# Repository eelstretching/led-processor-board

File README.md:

# LED processor board

The brains for the LED output boards: an RP2350B with an RM2 radio, 8 MB PSRAM, a DS3231 RTC and
four 16-pin ribbon shrouds. Each shroud drives one
[led-output-board](https://github.com/eelstretching/led-output-board), which does the level
shifting, fusing and strand connectors, so this board carries no LED power.

The core (RP2350B, flash, PSRAM, RM2, crystal, BOOTSEL/RUN buttons, 3.3 V regulator) is the
[rp2350b-rm2-reference](https://github.com/eelstretching/rp2350b-rm2-reference) schematic
unchanged, except that its micro-B USB is now USB-C. That board's single-row J2/J3 headers are
gone; the rest is new.

Status: **schematic and first layout done, not yet built.** ERC is clean apart from the four items
inherited from Pi's design, and DRC has no copper errors and nothing unconnected (see
"Verification").

All three sheets: [docs/schematic.pdf](docs/schematic.pdf) ([Power](docs/sheet-power.png), [Outputs](docs/sheet-outputs.png)).

## Pin map

| GPIO | Use |
|---|---|
| 0-7 | OUT1 (J5) data 1-8 |
| 8-15 | OUT2 (J6) data 1-8 |
| 16-23 | OUT3 (J7) data 1-8 |
| 24-31 | OUT4 (J8) data 1-8 |
| 32 | RTC SDA (I2C0), 10k pull-up |
| 33 | RTC SCL (I2C0), 10k pull-up |
| 34 | RTC INT/SQW, 10k pull-up (open drain) |
| 35-42 | J2 spare header (UART1 TX/RX on 36/37; 40-42 are ADC0-2) |
| 43-46 | RM2 (WL_ON + BT_ON, CS, DATA, CLK), as on the reference board |
| 47 | PSRAM chip select, as on the reference board |

All 32 outputs sit in GPIO 0-31, so one PIO block (GPIO base 0) reaches every output. The radio's
PIO uses the 16-47 window, so it has to be a different PIO block from the LED renderer's. The
board header is `firmware/boards/led_processor_board.h` (the reference board's `rp2350b_rm2.h`
plus the RTC pins); see [firmware/README.md](firmware/README.md) for the DS3231 driver and the
`rtc_set` firmware.

## Output shrouds (J5-J8)

The same pinout as the output boards' J2 (and MegaTree `docs/power.md`). Pin 1 is the triangle on
the shroud.

| Pin | Signal | Pin | Signal |
|---|---|---|---|
| 1 | GND | 2 | data 1 |
| 3 | GND | 4 | data 2 |
| 5 | GND | 6 | data 3 |
| 7 | GND | 8 | data 4 |
| 9 | GND | 10 | data 5 |
| 11 | GND | 12 | data 6 |
| 13 | +3V3 (shifter VCCA) | 14 | data 7 |
| 15 | +5V (shifter VCCB) | 16 | data 8 |

Data n of OUTk is GPIO 8(k-1) + (n-1). Each data line has a 33R series resistor at the RP2350 end
to damp ringing on the ribbon. Each shroud has 100n on +3V3 and on +5V.

## Power (Power sheet)

- **J4, 12 V in**, from the LED supply (through a PTC on an output board, as planned for the Pico
  boards). D3 (SS34) blocks a reversed lead.
- **U7, TPS54202H buck, 12 V to 5 V.** 4.5-28 V in, 2 A, SOT-23-6, with the values from TI's
  TPS54202HEVM-716 5 V design: 100k/13.3k divider (5.08 V), 75 pF feed-forward, 15 uH, 3 x 22 uF out,
  510k EN pull-up from 12 V. The load is well under 0.5 A.
- **+5V goes straight to pin 15 of every shroud**, and through D4 (B5819W) to VSYS, which feeds the
  existing NCP1117 3.3 V regulator. **+3V3 goes to pin 13 of every shroud.**
- D5 (green) shows +5V is up.
- USB still works for programming. On USB alone the board runs (VSYS through D2), but the ribbons
  get no +5V, so the output boards' shifters are off. D4 keeps USB from back-feeding the buck.

## USB

J1 is a USB-C receptacle (Korean Hroparts TYPE-C-31-M-12, LCSC C165948, KiCad's stock
`USB_C_Receptacle_HRO_TYPE-C-31-M-12` footprint) in place of Pi's micro-B. USB 2.0 only: D+ and D-
from both sides of the plug are joined, CC1 and CC2 each have a 5.1k pull-down (R56, R57) so a
USB-C charger or host turns on 5 V, SBU1/SBU2 are unconnected and the shell goes to GND. The
D+/D- nets (USB_D+/USB_D-, through Pi's 27R R7/R8) and VBUS into D2 are as before.

## RTC

The DS3231 circuit from universal-strip-controller (its U9): DS3231SN, 1 uF on VCC, 10k pull-ups on
SDA, SCL and INT/SQW, 32KHZ and RST unconnected. The coin cell is a CR1220 in a Keystone 3001 holder,
so it can be replaced (universal-strip-controller used a tabbed cell).

## Headers

- **J2, spare GPIO** (1x10, 2.54 mm): 3V3, GPIO35-42, GND.
- **J3, SWD** (1x3, 2.54 mm): SWCLK, GND, SWD, the same order as a Pico's debug header.
- **J9, RM2 spare GPIO** (1x3, 2.54 mm, under the board name, left of J3): WL_GPIO1, WL_GPIO2, GND. These are the
  radio chip's own pins, not RP2350 pins: set or read them with `cyw43_arch_gpio_put()` /
  `cyw43_arch_gpio_get()`, which go over the radio's SPI link, so they're slow, plain digital in/out
  (no PWM, PIO or ADC). Fine for an LED, a button or a relay in a pinch. On a Pico 2 W these two are
  SMPS mode and VBUS sense; here nothing else uses them.

## BOM / JLCPCB

`production/` holds the BOMs and the JLCPCB upload set. `bom-full.csv` is the full BOM with LCSC
numbers (edit this one); the rest is made from it and the board by
`python3 tools/jlc.py` (rerun it after any board change):

- `led-processor-board-gerbers.zip`: gerbers and drill files.
- `jlcpcb-bom.csv` and `jlcpcb-cpl.csv`: BOM and placement for the 111 SMD parts JLC assembles
  (everything on the top side with an LCSC number). JLC's 3D models don't always share KiCad's zero
  angle: `ROT_FIX` in `tools/jlc.py` turns U2, U3, U4 and U6 a quarter turn to match (checked in
  JLC's placement preview for the first order). Still check the preview: legs on pads, pink pin-1
  dot at the board's pin-1 mark.

`tools/jlc.py` needs KiCad's own Python (for `pcbnew`) and `kicad-cli` on the PATH. On a Mac with
KiCad in `/Applications/KiCad`, save the board in KiCad, then from the repo root:

```sh
K=/Applications/KiCad/KiCad.app/Contents
PATH=$K/MacOS:$PATH $K/Frameworks/Python.framework/Versions/Current/bin/python3 tools/jlc.py
git status production/   # see what changed, then commit and push
```

On Linux, with KiCad installed from its PPA, plain `python3 tools/jlc.py` works. The BOM and CPL
only change when parts move or the BOM changes; the gerbers zip changes with any copper or silk
edit.

Left off both files for hand-soldering:

- **U5 RM2**: buy Raspberry Pi SC1169, as on the reference board.
- **L1** Abracon AOTA-B201610S3R3-101-T, 3.3 uH (Digi-Key or Mouser): the part Pi specifies for the RP2350 core regulator, out of stock at LCSC when ordering (2026-10). It is polarized: match its dot to the footprint mark.
- **BT1** Keystone 3001 holder (Digi-Key 36-3001-ND).
- **J2, J3, J9** pin headers and **J5-J8** box headers (the shrouds already bought for the output
  boards).
- **J4** terminal block (C695629): JLC could fit it as through-hole assembly, but it's left to you.

SW1/SW2 are XKB TS-1088R-02526 (C455281, 4 x 3 mm) in place of Pi's Wurth 434133025816, which LCSC
doesn't stock; same spots, same nets. R1 is DNP, as on the reference board. Pi's R9 (an unfitted 0R option from GPIO0 to the flash chip
select) is removed, with its GPIO0 branch, so OUT1's first data line has no stub. The PSRAM chip
select is GPIO47 (QMI CS1n, RP2350 datasheet section 9.4, which allows GPIO 0, 8, 19 or 47).

J4 (DORABO DB301V-3.5-2P, C695629) is in the same family as the output boards' strand terminals and
uses KiCad's stock 3.5 mm Phoenix PT footprint; check the hole size against the DB301V drawing when
laying out.

## Layout

100 x 89.5 mm, **2 layers**, four 2.75 mm (M2.5) mounting holes. 3D views:
[top](docs/pcb-3d-top.png), [bottom](docs/pcb-3d-bottom.png); bottom copper:
[docs/pcb-bottom-copper.png](docs/pcb-bottom-copper.png).

- **The core is Pi's layout**: the RP2350B, flash, crystal, regulator, buttons and RM2 keep their
  placement and routing from the reference board (the buttons are a stock LCSC part in Pi's spots).
  The one move: **U4 (PSRAM), C22, R11 and R13
  moved from under the flash to the top side**, just left of it, so every part is on the top and
  JLCPCB can assemble one side. The PSRAM's QSPI branches are about 12-15 mm long; Pi's were vias
  straight down to it. Pi's +3V3 top pour and full GND bottom plane stay; the board widens with a top
  GND pour on either side, stitched to the bottom plane.
- **Shrouds**: OUT1/OUT2 (J5, J6) down the left edge, OUT3/OUT4 (J7, J8) along the bottom, either
  side of the RM2 antenna. The bottom two sit as low as the antenna strip allows (their bottom pins
  stop just above it, their bodies overhang it); J8 is 1.6 mm left of the resistor row to clear the
  corner hole, so its data lines jog. The 33R resistors sit in a row next to each shroud's data
  pins. On J7/J8 the 3V3 and 5V runs use the channel between the two pin rows, one net per layer.
- **Power** in the top right: J4 (12 V) on the right edge, D3, the TPS54202 buck (U7, L2, output
  caps) and D5. The 12 V runs are 0.8 mm, +5V 0.5 mm.
- **USB-C** at the top edge where Pi's micro-B was, with **J2 (spare GPIO35-42, plus 3V3 and GND)**
  along the top edge to its right, so wires leave from the board edge. Its lines leave the core on
  the top layer, drop through a row of vias left of the buck and fan out on the bottom; the ADC pins
  (GPIO40-42) are the lanes furthest from the buck's switch node. The RTC (U6, BT1) is on the right
  and J9 (RM2 spare GPIO) and J3 (SWD) sit side by side under the board name.
- The antenna keepout runs the full width along the bottom edge past the RM2.

### Regenerating it

The layout was built by scripts in `tools/pcb/` (KiCad 10 Python API plus Freerouting 1.9.0). From
here on it is a normal KiCad board, so edit it in KiCad; the scripts are a record of how it was made.

1. `build_pcb.py REF.kicad_pcb net.xml OUT.kicad_pcb .` loads the reference layout, drops its
   micro-B and headers, clips the routes that went to them, places the new parts
   (`placement.py`) and hand-routes the power, USB-C, OUT4, RM2 and SWD runs (`preroute.py`).
   `net.xml` is `kicad-cli sch export netlist --format kicadxml`.
2. `route.sh in out 20` exports a Specctra DSN, freezes the existing copper and sets net classes
   (`dsn_prep.py`), runs Freerouting 1.9.0 (`xvfb-run java -jar freerouting-1.9.0.jar`; 2.x
   ignores the pass limit and never writes the session), and imports the result.
3. `post.py` trims dangling tails and adds GND stitching vias; `fix.py` adds the two +3V3 jumpers
   under the +5V run to J7 and C40's link; `rip.py` plus a second `route.sh` rerouted the J2/RTC
   fan-out (GPIO32-42), which the first pass left one net short on; `silk.py` places the reference
   designators.
4. Moving the PSRAM to the top: `psram.py` (flip and place U4/C22/R11/R13, rip their bottom-side
   routing), `post.py --trim-only`, `psram2.py` (Pi's QSPI escapes from under U3, the GPIO47 drop),
   `route.sh`, then the U4 supply hop at the end of `fix.py`, `post.py` and `silk.py`.
5. Moving J2 to the top edge: `j2top.py` (place it and its pin labels, rip its old fan-out),
   `post.py --trim-only`, `j2route.py` (hand-routes the bus and moves the +3V3 hop from the core pour
   to the RTC, which also feeds the lower pour and the RM2, below the via row), `post.py`, `silk.py`.
6. Bottom shrouds to the edge and J9: `shrouds.py` (move J7/J8 and their caps, re-run the data
   lines, rip their power), `shrouds2.py` (hand-routes their 3V3/5V), `post.py`, `silk.py`, then
   `hdrs.py` (adds J9 and moves J3 under the board name), `route.sh` (WL_GPIO1/2), `post.py`,
   `silk.py`, and `swd.py` (hand-routes SWCLK/SWD, which Freerouting couldn't get out of the core).
7. LCSC buttons: `buttons.py` (TS-1088R footprints in SW1/SW2's spots, stubs re-joined) and
   `tools/sch_buttons.py` (swaps the schematic symbols to `Switch:SW_Push`).
8. `tools/rm_r9.py` drops R9 and its GPIO0 branch from the schematic and board; `tidy_gpio.py`
   straightens GPIO0 and chamfers GPIO1 on their way to OUT1.
9. `render.sh` / `rendernz.sh` make the PNGs (`kicad-cli pcb export svg` cropped with cairosvg;
   `rendernz` hides zone fills).

## Files

| Path | What |
|---|---|
| `led-processor-board.kicad_sch` | root sheet: the reference core, RTC, J2/J3/J9, sheet symbols |
| `Power.kicad_sch` | 12 V in, buck, +5V, VSYS |
| `Outputs.kicad_sch` | J5-J8 shrouds, 33R series resistors, decoupling |
| `rp2350b_rm2.kicad_sym`, `rp2350b_rm2.pretty/` | RM2 symbol and footprint (from the reference) |
| `production/bom-full.csv` | full BOM with LCSC numbers |
| `production/` (rest) | JLCPCB gerbers zip, assembly BOM and CPL (`tools/jlc.py`) |
| `docs/schematic.pdf`, `docs/sheet-*.png` | all three sheets |
| `led-processor-board.kicad_pcb` | the layout |
| `docs/pcb-*.png` | layout previews |
| `tools/build_schematic.py` | the one-off script that built these sheets from the reference (kept for reference; edit the schematic in KiCad from here on) |
| `tools/pcb/` | the scripts that built the layout (see "Regenerating it") |

## Verification

`kicad-cli sch erc` (KiCad 10.0.7, stock libraries) reports the same four items as the reference
board, all in Pi's part of the design: U2's two OUT pins tied together, U1 VREG_AVDD and #PWR16
"not driven" (power-flag nits), and one off-grid wire end. The rest are notes that Pi's embedded
libraries (`RPI_DB`, `RPI - Power`, `RPI_COMPILED`) aren't in the library table, as on the
reference board. A netlist check confirms each shroud's GND, +3V3, +5V and data pins, the RTC nets
and the 12 V to VSYS chain.

`kicad-cli pcb drc --severity-all --schematic-parity` reports no clearance, short, hole or unconnected
items, and the board matches the schematic (apart from footprints not carrying the symbols'
`manufacturer` fields). What's
left: 41 warnings that Pi's `RPI_COMPILED` footprint library isn't in the library table (as on the
reference board), and 4 silkscreen-past-the-edge warnings from J1 and J4, whose bodies overhang the
board edge (the USB-C opening and the terminal block). C7 and C27 have their reference designators hidden
for lack of room.

## License

Raspberry Pi's design is MIT (see `LICENSE-RaspberryPi.txt`); the additions here are MIT too.

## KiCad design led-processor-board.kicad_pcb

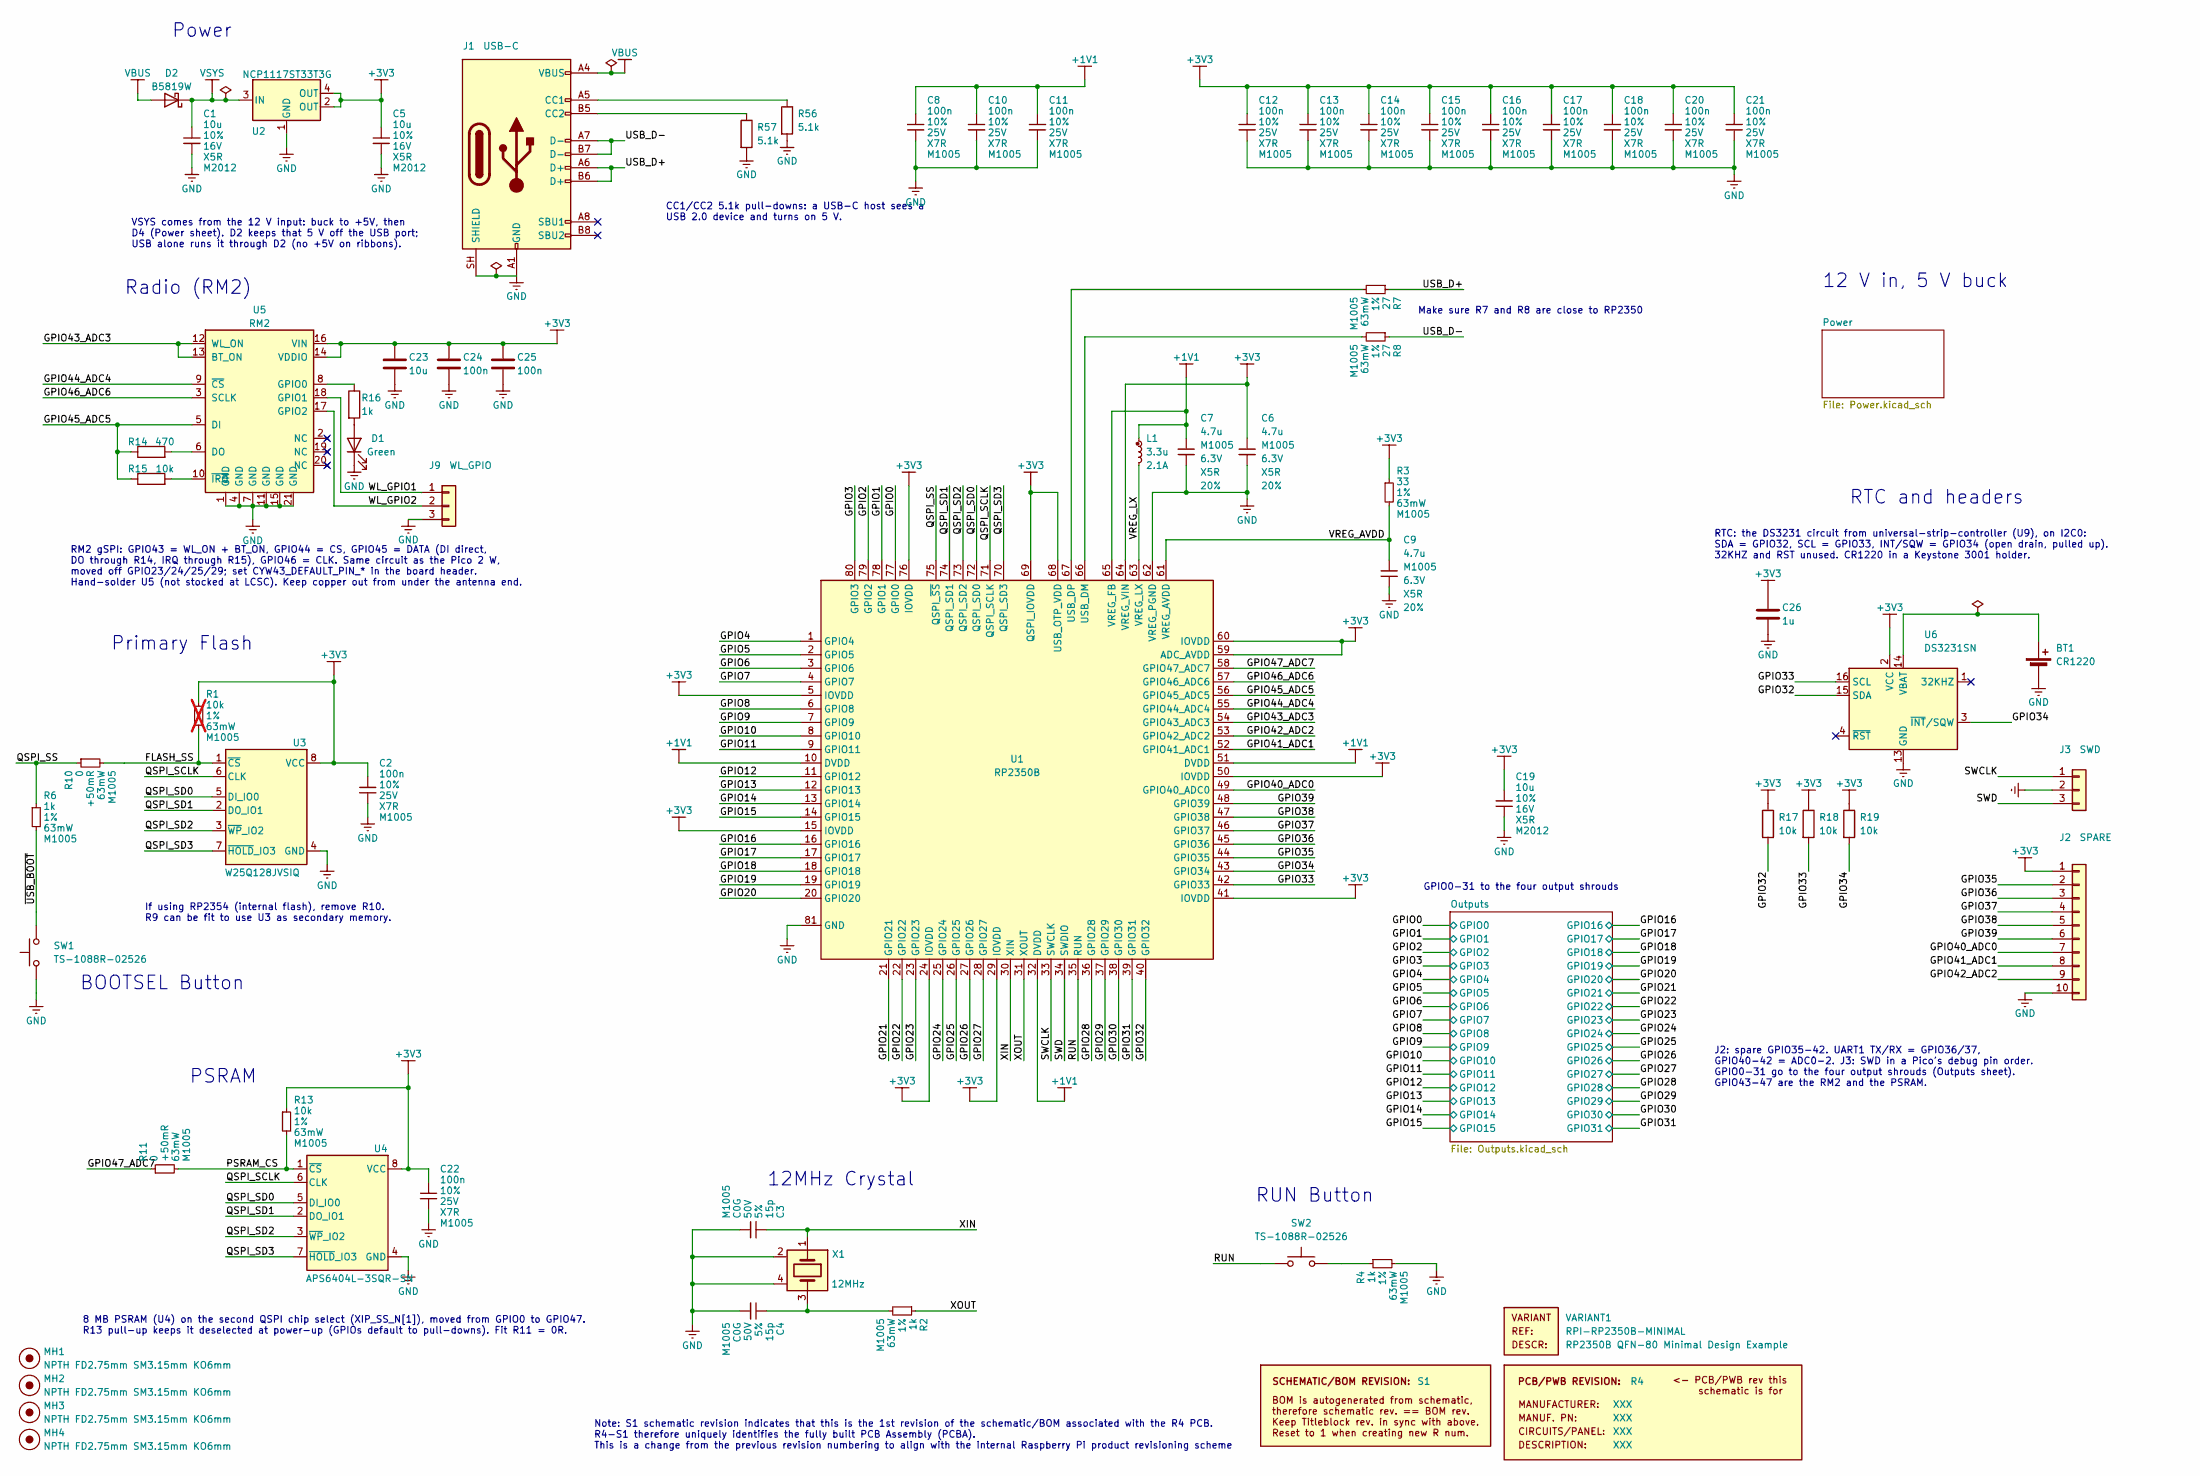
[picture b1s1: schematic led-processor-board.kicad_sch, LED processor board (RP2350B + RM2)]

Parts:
BT1: CR1220; BatteryHolder_Keystone_3001_1x12mm; manufacturer_pn 3001
C1, C5, C19: 10u; generic_capc2012x125; voltage 16V; tolerance 10%; part_uid RP-01GYSK-AVBE41; LCSC C15850
C2, C8, C10, C11, C12, C13, C14, C15, C16, C17, C18, C20, C21, C22: 100n; generic_capc1005x50; voltage 25V; tolerance 10%; part_uid RP-01BJ9Y-KRGF41; LCSC C1525
C3, C4: 15p; generic_capc1005x50; voltage 50V; tolerance 5%; part_uid RP-01C89W-LLY9XV; LCSC C1548
C6, C7: 4.7u; generic_capc1005x50_wide; voltage 6.3V; tolerance 20%; part_uid RP-019A1P-0C2GHY; LCSC C23733
C9: 4.7u; generic_capc1005x50; voltage 6.3V; tolerance 20%; part_uid RP-019A1P-0C2GHY; LCSC C23733
C23: 10u; C_0805_2012Metric; manufacturer_pn CL21A106KAYNNNE; LCSC C15850
C24, C25: 100n; C_0402_1005Metric; manufacturer_pn CL05B104KO5NNNC; LCSC C1525
C26: 1u; C_0402_1005Metric; manufacturer_pn CL05A105KA5NQNC; LCSC C52923
D1: Green; LED_0603_1608Metric; manufacturer_pn KT-0603YG; LCSC C2289
D2: B5819W; D_SOD-123; manufacturer_pn B5819W SL; LCSC C8598
J1: USB-C; USB_C_Receptacle_HRO_TYPE-C-31-M-12; manufacturer_pn TYPE-C-31-M-12; LCSC C165948
J2: SPARE; PinHeader_1x10_P2.54mm_Vertical; manufacturer_pn 1x10 2.54 mm pin header
J3: SWD; PinHeader_1x03_P2.54mm_Vertical; manufacturer_pn 1x3 2.54 mm pin header
J9: WL_GPIO; PinHeader_1x03_P2.54mm_Vertical; manufacturer_pn 1x3 2.54 mm pin header
L1: 3.3u; abracon_aota-b201610s3r3-101-t; tolerance 20%; part_uid RP-01GY5D-2VC7WP; LCSC C42411119
MH1, MH2, MH3, MH4: NPTH FD2.75mm SM3.15mm KO6mm; none_mh_npth_fd2p75mm_sm3p15mm_ko6mm; part_uid RP-01HF5R-LCTEJS
PCB1: R4; manufacturer_pn XXX
R1: 10k; generic_resc1005x35; tolerance 1%; voltage 50V; part_uid RP-019A1P-53DHSX; LCSC C25744; not fitted
R2, R4, R6: 1k; generic_resc1005x35; tolerance 1%; voltage 50V; part_uid RP-019A1P-4Z6ZWY; LCSC C11702
R3: 33; generic_resc1005x35; tolerance 1%; voltage 50V; part_uid RP-019A1P-58PW9L; LCSC C25105
R7, R8: 27; generic_resc1005x35; tolerance 1%; voltage 50V; part_uid RP-01C89V-LTEYC4; LCSC C25100
R10, R11: 0; generic_resc1005x35; tolerance +50mR; voltage 50V; part_uid RP-019A1P-4Y4V63; LCSC C17168
R13: 10k; generic_resc1005x35; tolerance 1%; voltage 50V; part_uid RP-019A1P-53DHSX; LCSC C25744
R14: 470; R_0402_1005Metric; manufacturer_pn 0402WGF4700TCE; LCSC C25117
R15, R17, R18, R19: 10k; R_0402_1005Metric; manufacturer_pn 0402WGF1002TCE; LCSC C25744
R16: 1k; R_0402_1005Metric; manufacturer_pn 0402WGF1001TCE; LCSC C11702
R56, R57: 5.1k; R_0402_1005Metric; manufacturer_pn 0402WGF5101TCE; LCSC C25905
SBREV1: S1
SW1, SW2: TS-1088R-02526; SW_SPST_TS-1088-xR025; manufacturer_pn TS-1088R-02526; LCSC C455281
U1: RP2350B; rpi_rp2350b_vias; part_uid RP-01HA9H-ABBLJN; LCSC C42415655
U2: NCP1117ST33T3G; onsemi_ncp1117st33t3g; voltage 3.3V; part_uid RP-01JWD9-7JRX6J; LCSC C26537
U3: W25Q128JVSIQ; generic_soic127p790x195-8; voltage 2.7-3.6V; part_uid RP-01JWD4-F1H4N9; LCSC C97521
U4: APS6404L-3SQR-SN; SOIC-8_3.9x4.9mm_P1.27mm; voltage 2.7-3.6V; manufacturer_pn APS6404L-3SQR-SN; LCSC C5333729
U5: RM2; RPi_RM2; manufacturer_pn SC1169 (RMC20452T)
U6: DS3231SN; SOIC-16W_7.5x10.3mm_P1.27mm; manufacturer_pn DS3231SN#T&R; LCSC C9866
VARIANT1: RPI-RP2350B-MINIMAL
X1: 12MHz; generic_xtalcc320x250x80-4; tolerance 30ppm; part_uid RP-01G8X7-GS352B; LCSC C20625731

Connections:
+1V1: C7.1, C8.1, C10.1, C11.1, L1.1, U1.10 (DVDD), U1.32 (DVDD), U1.51 (DVDD), U1.65 (VREG_FB)
+3V3: C2.1, C5.1, C6.1, C12.1, C13.1, C14.1, C15.1, C16.1, C17.1, C18.1, C19.1, C20.1, C21.1, C22.1, C23.1, C24.1, C25.1, C26.1, J2.1, R1.1, R3.1, R13.1, R17.1, R18.1, R19.1, U1.5 (IOVDD), U1.15 (IOVDD), U1.24 (IOVDD), U1.29 (IOVDD), U1.41 (IOVDD), U1.50 (IOVDD), U1.59 (ADC_AVDD), U1.60 (IOVDD), U1.64 (VREG_VIN), U1.68 (USB_OTP_VDD), U1.69 (QSPI_IOVDD), U1.76 (IOVDD), U2.2 (OUT), U2.4 (OUT), U3.8 (VCC), U4.8 (VCC), U5.14 (VDDIO), U5.16 (VIN), U6.2 (VCC); also elsewhere on the board
/FLASH_SS: R1.2, R10.2, U3.1 (~CS)
/GPIO0: U1.77 (GPIO0); also elsewhere on the board
/GPIO1: U1.78 (GPIO1); also elsewhere on the board
/GPIO2: U1.79 (GPIO2); also elsewhere on the board
/GPIO3: U1.80 (GPIO3); also elsewhere on the board
/GPIO4: U1.1 (GPIO4); also elsewhere on the board
/GPIO5: U1.2 (GPIO5); also elsewhere on the board
/GPIO6: U1.3 (GPIO6); also elsewhere on the board
/GPIO7: U1.4 (GPIO7); also elsewhere on the board
/GPIO8: U1.6 (GPIO8); also elsewhere on the board
/GPIO9: U1.7 (GPIO9); also elsewhere on the board
/GPIO10: U1.8 (GPIO10); also elsewhere on the board
/GPIO11: U1.9 (GPIO11); also elsewhere on the board
/GPIO12: U1.11 (GPIO12); also elsewhere on the board
/GPIO13: U1.12 (GPIO13); also elsewhere on the board
/GPIO14: U1.13 (GPIO14); also elsewhere on the board
/GPIO15: U1.14 (GPIO15); also elsewhere on the board
/GPIO16: U1.16 (GPIO16); also elsewhere on the board
/GPIO17: U1.17 (GPIO17); also elsewhere on the board
/GPIO18: U1.18 (GPIO18); also elsewhere on the board
/GPIO19: U1.19 (GPIO19); also elsewhere on the board
/GPIO20: U1.20 (GPIO20); also elsewhere on the board
/GPIO21: U1.21 (GPIO21); also elsewhere on the board
/GPIO22: U1.22 (GPIO22); also elsewhere on the board
/GPIO23: U1.23 (GPIO23); also elsewhere on the board
/GPIO24: U1.25 (GPIO24); also elsewhere on the board
/GPIO25: U1.26 (GPIO25); also elsewhere on the board
/GPIO26: U1.27 (GPIO26); also elsewhere on the board
/GPIO27: U1.28 (GPIO27); also elsewhere on the board
/GPIO28: U1.36 (GPIO28); also elsewhere on the board
/GPIO29: U1.37 (GPIO29); also elsewhere on the board
/GPIO30: U1.38 (GPIO30); also elsewhere on the board
/GPIO31: U1.39 (GPIO31); also elsewhere on the board
/GPIO32: R17.2, U1.40 (GPIO32), U6.15 (SDA)
/GPIO33: R18.2, U1.42 (GPIO33), U6.16 (SCL)
/GPIO34: R19.2, U1.43 (GPIO34), U6.3 (~INT/SQW)
/GPIO35: J2.2, U1.44 (GPIO35)
/GPIO36: J2.3, U1.45 (GPIO36)
/GPIO37: J2.4, U1.46 (GPIO37)
/GPIO38: J2.5, U1.47 (GPIO38)
/GPIO39: J2.6, U1.48 (GPIO39)
/GPIO40_ADC0: J2.7, U1.49 (GPIO40_ADC0)
/GPIO41_ADC1: J2.8, U1.52 (GPIO41_ADC1)
/GPIO42_ADC2: J2.9, U1.53 (GPIO42_ADC2)
/GPIO43_ADC3: U1.54 (GPIO43_ADC3), U5.12 (WL_ON), U5.13 (BT_ON)
/GPIO44_ADC4: U1.55 (GPIO44_ADC4), U5.9 (~CS)
/GPIO45_ADC5: R14.1, R15.1, U1.56 (GPIO45_ADC5), U5.5 (DI)
/GPIO46_ADC6: U1.57 (GPIO46_ADC6), U5.3 (SCLK)
/GPIO47_ADC7: R11.1, U1.58 (GPIO47_ADC7)
/PSRAM_CS: R11.2, R13.2, U4.1 (~CS)
/QSPI_SCLK: U1.71 (QSPI_SCLK), U3.6 (CLK), U4.6 (CLK)
/QSPI_SD0: U1.72 (QSPI_SD0), U3.5 (DI_IO0), U4.5 (DI_IO0)
/QSPI_SD1: U1.74 (QSPI_SD1), U3.2 (DO_IO1), U4.2 (DO_IO1)
/QSPI_SD2: U1.73 (QSPI_SD2), U3.3 (~WP_IO2), U4.3 (~WP_IO2)
/QSPI_SD3: U1.70 (QSPI_SD3), U3.7 (~HOLD_IO3), U4.7 (~HOLD_IO3)
/QSPI_SS: R6.1, R10.1, U1.75 (QSPI_~SS)
/RUN: SW2.2, U1.35 (RUN)
/SWCLK: J3.1, U1.33 (SWCLK)
/SWD: J3.3, U1.34 (SWDIO)
/USB_D+: J1.A6 (D+), J1.B6 (D+), R7.1
/USB_D-: J1.A7 (D-), J1.B7 (D-), R8.1
/VREG_AVDD: C9.1, R3.2, U1.61 (VREG_AVDD)
/VREG_LX: L1.2, U1.63 (VREG_LX)
/WL_GPIO1: J9.1, U5.18 (GPIO1)
/WL_GPIO2: J9.2, U5.17 (GPIO2)
/XIN: C3.1, U1.30 (XIN), X1.1
/XOUT: R2.1, U1.31 (XOUT)
/~USB_BOOT: R6.2, SW1.2
GND: BT1.2 (-), C1.2, C2.2, C3.2, C4.2, C5.2, C6.2, C7.2, C8.2, C9.2, C10.2, C11.2, C12.2, C13.2, C14.2, C15.2, C16.2, C17.2, C18.2, C19.2, C20.2, C21.2, C22.2, C23.2, C24.2, C25.2, C26.2, D1.1 (K), J1.A1 (GND), J1.A12 (GND), J1.B1 (GND), J1.B12 (GND), J1.SH (SHIELD), J2.10, J3.2, J9.3, R4.2, R56.2, R57.2, SW1.1, U1.62 (VREG_PGND), U1.81 (GND), U2.1 (GND), U3.4 (GND), U4.4 (GND), U5.1 (GND), U5.4 (GND), U5.7 (GND), U5.11 (GND), U5.15 (GND), U5.21 (GND), U6.5 (GND), U6.6 (GND), U6.7 (GND), U6.8 (GND), U6.9 (GND), U6.10 (GND), U6.11 (GND), U6.12 (GND), U6.13 (GND), X1.2, X1.4; also elsewhere on the board
unnamed: BT1.1 (+), U6.14 (VBAT)
unnamed: C4.1, R2.2, X1.3
unnamed: D1.2 (A), R16.2
unnamed: J1.A5 (CC1), R56.1
unnamed: J1.B5 (CC2), R57.1
unnamed: R4.1, SW2.1
unnamed: R8.2, U1.66 (USB_DM)
unnamed: R7.2, U1.67 (USB_DP)
unnamed: R14.2, U5.6 (DO)
unnamed: R16.1, U5.8 (GPIO0)
unnamed: R15.2, U5.10 (~IRQ)
VBUS: D2.2 (A), J1.A4 (VBUS), J1.A9 (VBUS), J1.B4 (VBUS), J1.B9 (VBUS)
VSYS: C1.1, D2.1 (K), U2.3 (IN); also elsewhere on the board

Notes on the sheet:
8 MB PSRAM (U4) on the second QSPI chip select (XIP_SS_N[1]), moved from GPIO0 to GPIO47. R13 pull-up keeps it deselected at power-up (GPIOs default to pull-downs). Fit R11 = 0R.
RTC and headers
If using RP2354 (internal flash), remove R10. R9 can be fit to use U3 as secondary memory.
Note: S1 schematic revision indicates that this is the 1st revision of the schematic/BOM associated with the R4 PCB. R4-S1 therefore uniquely identifies the fully built PCB Assembly (PCBA). This is a change from the previous revision numbering to align with the internal Raspberry Pi product revisio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
Radio (RM2)
RUN Button
RM2 gSPI: GPIO43 = WL_ON + BT_ON, GPIO44 = CS, GPIO45 = DATA (DI direct, DO through R14, IRQ through R15), GPIO46 = CLK. Same circuit as the Pico 2 W, moved off GPIO23/24/25/29; set CYW43_DEFAULT_PIN_* in the board header. Hand-solder U5 (not stocked at LCSC). Keep copper out from under the antenna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
Primary Flash
BOOTSEL Button
12MHz Crystal
Make sure R7 and R8 are close to RP2350
PSRAM
Power
VSYS comes from the 12 V input: buck to +5V, then D4 (Power sheet). D2 keeps that 5 V off the USB port; USB alone runs it through D2 (no +5V on ribbons).
RTC: the DS3231 circuit from universal-strip-controller (U9), on I2C0: SDA = GPIO32, SCL = GPIO33, INT/SQW = GPIO34 (open drain, pulled up). 32KHZ and RST unused. CR1220 in a Keystone 3001 holder.
J2: spare GPIO35-42. UART1 TX/RX = GPIO36/37, GPIO40-42 = ADC0-2. J3: SWD in a Pico's debug pin order. GPIO0-31 go to the four output shrouds (Outputs sheet). GPIO43-47 are the RM2 and the PSRAM.
CC1/CC2 5.1k pull-downs: a USB-C host sees a USB 2.0 device and turns on 5 V.
GPIO0-31 to the four output shrouds
12 V in, 5 V buck

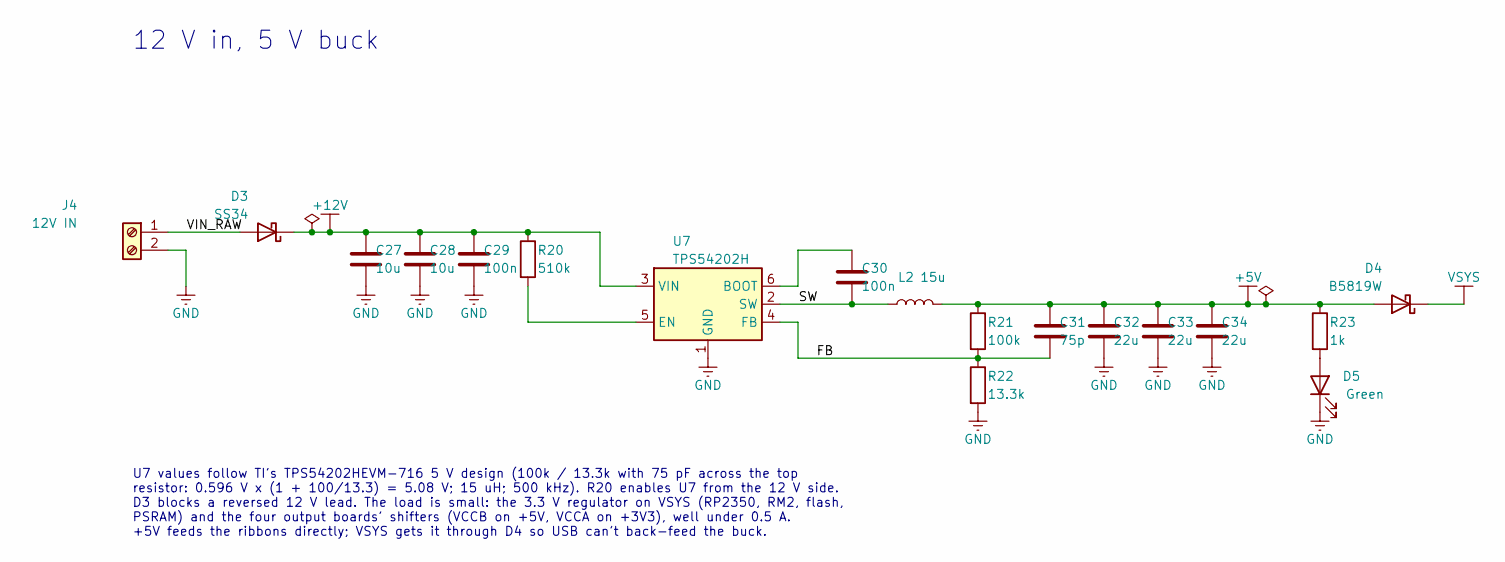
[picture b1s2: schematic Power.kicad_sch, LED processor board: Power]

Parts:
C27, C28: 10u; C_0805_2012Metric; manufacturer_pn CL21A106KBYNNNE; LCSC C440198
C29, C30: 100n; C_0603_1608Metric; manufacturer_pn CC0603KRX7R9BB104; LCSC C14663
C31: 75p; C_0402_1005Metric; manufacturer_pn 0402CG750J500NT; LCSC C37809
C32, C33, C34: 22u; C_0805_2012Metric; manufacturer_pn CL21A226MAQNNNE; LCSC C45783
D3: SS34; D_SMA; manufacturer_pn SS34; LCSC C8678
D4: B5819W; D_SOD-123; manufacturer_pn B5819W SL; LCSC C8598
D5: Green; LED_0603_1608Metric; manufacturer_pn KT-0603YG; LCSC C2289
J4: 12V IN; TerminalBlock_Phoenix_PT-1,5-2-3.5-H_1x02_P3.50mm_Horizontal; manufacturer_pn DB301V-3.5-2P-GN-S; LCSC C695629
L2: 15u; L_Sunlord_SWPA8040S; manufacturer_pn SWPA8040S150MT; LCSC C16853
R20: 510k; R_0402_1005Metric; manufacturer_pn 0402WGF5103TCE; LCSC C11616
R21: 100k; R_0402_1005Metric; manufacturer_pn 0402WGF1003TCE; LCSC C25741
R22: 13.3k; R_0402_1005Metric; manufacturer_pn 0402WGF1332TCE; LCSC C122547
R23: 1k; R_0402_1005Metric; manufacturer_pn 0402WGF1001TCE; LCSC C11702
U7: TPS54202H; SOT-23-6; manufacturer_pn TPS54202HDDCR; LCSC C527684

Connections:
+5V: C31.1, C32.1, C33.1, C34.1, D4.2 (A), L2.2, R21.1, R23.1; also elsewhere on the board
+12V: C27.1, C28.1, C29.1, D3.1 (K), R20.1, U7.3 (VIN)
/Power/FB: C31.2, R21.2, R22.1, U7.4 (FB)
/Power/SW: C30.2, L2.1, U7.2 (SW)
/Power/VIN_RAW: D3.2 (A), J4.1
GND: C27.2, C28.2, C29.2, C32.2, C33.2, C34.2, D5.1 (K), J4.2, R22.2, U7.1 (GND); also elsewhere on the board
unnamed: D5.2 (A), R23.2
unnamed: C30.1, U7.6 (BOOT)
unnamed: R20.2, U7.5 (EN)
VSYS: D4.1 (K); also elsewhere on the board

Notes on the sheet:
12 V in, 5 V buck
U7 values follow TI's TPS54202HEVM-716 5 V design (100k / 13.3k with 75 pF across the top resistor: 0.596 V x (1 + 100/13.3) = 5.08 V; 15 uH; 500 kHz). R20 enables U7 from the 12 V side. D3 blocks a reversed 12 V lead. The load is small: the 3.3 V regulator on VSYS (RP2350, RM2, flash, PSRAM) and t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

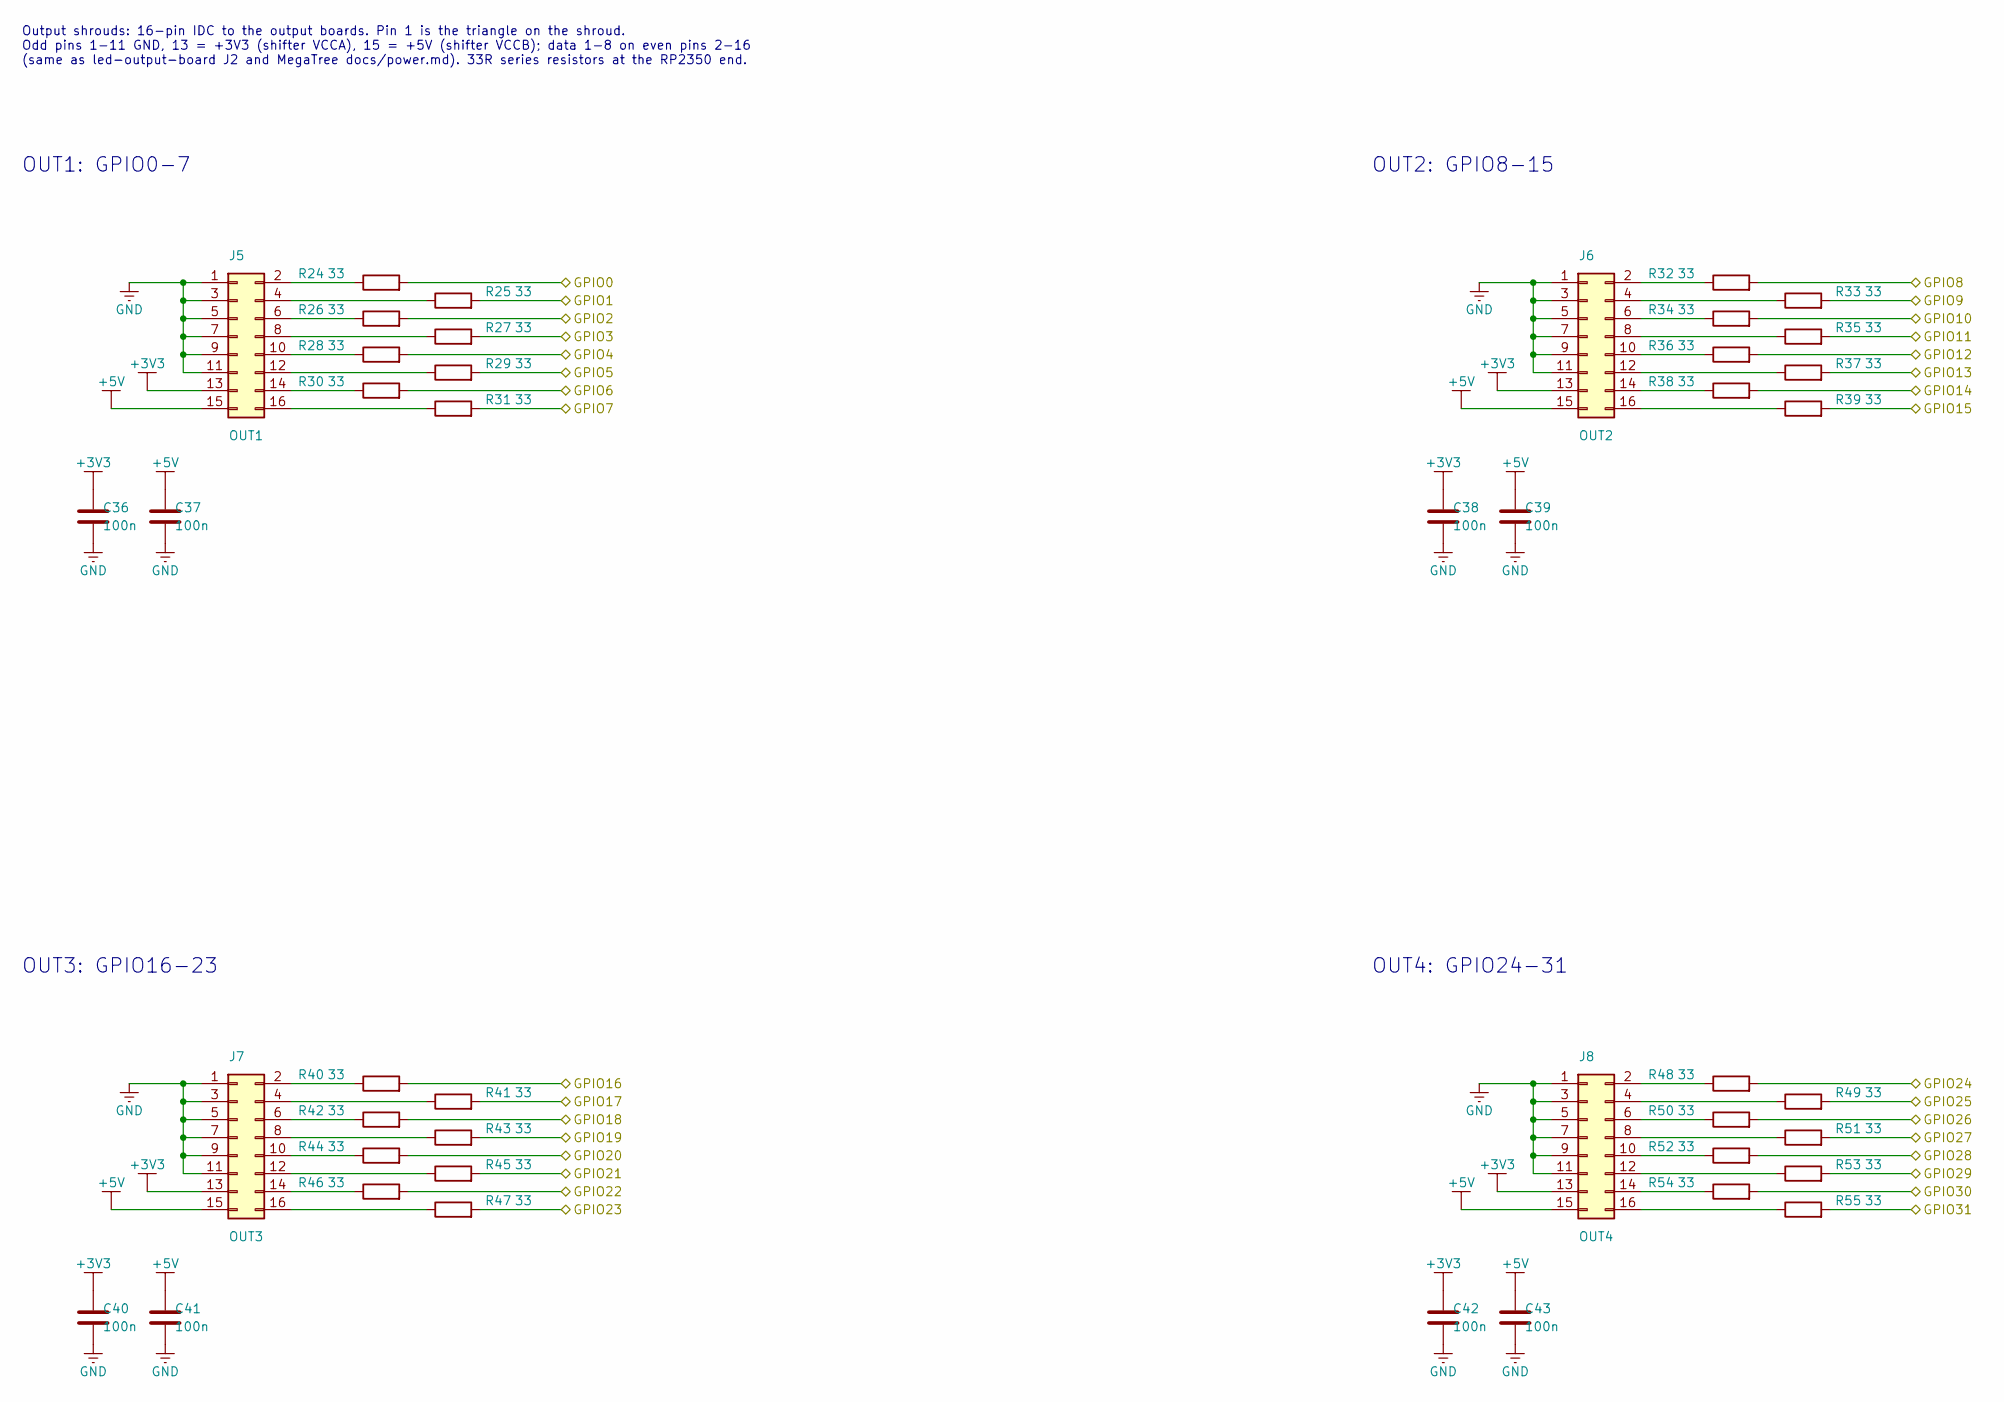
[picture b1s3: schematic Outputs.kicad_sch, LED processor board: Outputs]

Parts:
C36, C37, C38, C39, C40, C41, C42, C43: 100n; C_0402_1005Metric; manufacturer_pn CL05B104KO5NNNC; LCSC C1525
J5: OUT1; IDC-Header_2x08_P2.54mm_Vertical; manufacturer_pn Box header 2x08 2.54 mm
J6: OUT2; IDC-Header_2x08_P2.54mm_Vertical; manufacturer_pn Box header 2x08 2.54 mm
J7: OUT3; IDC-Header_2x08_P2.54mm_Vertical; manufacturer_pn Box header 2x08 2.54 mm
J8: OUT4; IDC-Header_2x08_P2.54mm_Vertical; manufacturer_pn Box header 2x08 2.54 mm
R24, R25, R26, R27, R28, R29, R30, R31, R32, R33, R34, R35, R36, R37, R38, R39, R40, R41, R42, R43, R44, R45, R46, R47, R48, R49, R50, R51, R52, R53, R54, R55: 33; R_0402_1005Metric; manufacturer_pn 0402WGF330JTCE; LCSC C25105

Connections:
+3V3: C36.1, C38.1, C40.1, C42.1, J5.13, J6.13, J7.13, J8.13; also elsewhere on the board
+5V: C37.1, C39.1, C41.1, C43.1, J5.15, J6.15, J7.15, J8.15; also elsewhere on the board
/GPIO0: R24.2; also elsewhere on the board
/GPIO1: R25.2; also elsewhere on the board
/GPIO2: R26.2; also elsewhere on the board
/GPIO3: R27.2; also elsewhere on the board
/GPIO4: R28.2; also elsewhere on the board
/GPIO5: R29.2; also elsewhere on the board
/GPIO6: R30.2; also elsewhere on the board
/GPIO7: R31.2; also elsewhere on the board
/GPIO8: R32.2; also elsewhere on the board
/GPIO9: R33.2; also elsewhere on the board
/GPIO10: R34.2; also elsewhere on the board
/GPIO11: R35.2; also elsewhere on the board
/GPIO12: R36.2; also elsewhere on the board
/GPIO13: R37.2; also elsewhere on the board
/GPIO14: R38.2; also elsewhere on the board
/GPIO15: R39.2; also elsewhere on the board
/GPIO16: R40.2; also elsewhere on the board
/GPIO17: R41.2; also elsewhere on the board
/GPIO18: R42.2; also elsewhere on the board
/GPIO19: R43.2; also elsewhere on the board
/GPIO20: R44.2; also elsewhere on the board
/GPIO21: R45.2; also elsewhere on the board
/GPIO22: R46.2; also elsewhere on the board
/GPIO23: R47.2; also elsewhere on the board
/GPIO24: R48.2; also elsewhere on the board
/GPIO25: R49.2; also elsewhere on the board
/GPIO26: R50.2; also elsewhere on the board
/GPIO27: R51.2; also elsewhere on the board
/GPIO28: R52.2; also elsewhere on the board
/GPIO29: R53.2; also elsewhere on the board
/GPIO30: R54.2; also elsewhere on the board
/GPIO31: R55.2; also elsewhere on the board
GND: C36.2, C37.2, C38.2, C39.2, C40.2, C41.2, C42.2, C43.2, J5.1, J5.3, J5.5, J5.7, J5.9, J5.11, J6.1, J6.3, J6.5, J6.7, J6.9, J6.11, J7.1, J7.3, J7.5, J7.7, J7.9, J7.11, J8.1, J8.3, J8.5, J8.7, J8.9, J8.11; also elsewhere on the board
unnamed: J5.2, R24.1
unnamed: J5.4, R25.1
unnamed: J5.6, R26.1
unnamed: J5.8, R27.1
unnamed: J5.10, R28.1
unnamed: J5.12, R29.1
unnamed: J5.14, R30.1
unnamed: J5.16, R31.1
unnamed: J6.2, R32.1
unnamed: J6.4, R33.1
unnamed: J6.6, R34.1
unnamed: J6.8, R35.1
unnamed: J6.10, R36.1
unnamed: J6.12, R37.1
unnamed: J6.14, R38.1
unnamed: J6.16, R39.1
unnamed: J7.2, R40.1
unnamed: J7.4, R41.1
unnamed: J7.6, R42.1
unnamed: J7.8, R43.1
unnamed: J7.10, R44.1
unnamed: J7.12, R45.1
unnamed: J7.14, R46.1
unnamed: J7.16, R47.1
unnamed: J8.2, R48.1
unnamed: J8.4, R49.1
unnamed: J8.6, R50.1
unnamed: J8.8, R51.1
unnamed: J8.10, R52.1
unnamed: J8.12, R53.1
unnamed: J8.14, R54.1
unnamed: J8.16, R55.1

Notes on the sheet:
Output shrouds: 16-pin IDC to the output boards. Pin 1 is the triangle on the shroud. Odd pins 1-11 GND, 13 = +3V3 (shifter VCCA), 15 = +5V (shifter VCCB); data 1-8 on even pins 2-16 (same as led-output-board J2 and MegaTree docs/power.md). 33R series resistors at the RP2350 end.
OUT1: GPIO0-7
OUT2: GPIO8-15
OUT3: GPIO16-23
OUT4: GPIO24-31
